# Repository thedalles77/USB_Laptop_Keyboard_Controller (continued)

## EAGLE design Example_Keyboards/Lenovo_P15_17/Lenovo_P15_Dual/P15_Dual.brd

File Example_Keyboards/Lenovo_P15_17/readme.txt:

Use the Lenovo_P15 files for a standard USB keyboard.
The P15_Dual folder is for a separate project that switches a P15 keyboard to its motherboard
or to a different computer that receives the keyboard signals over USB from the Teensy.

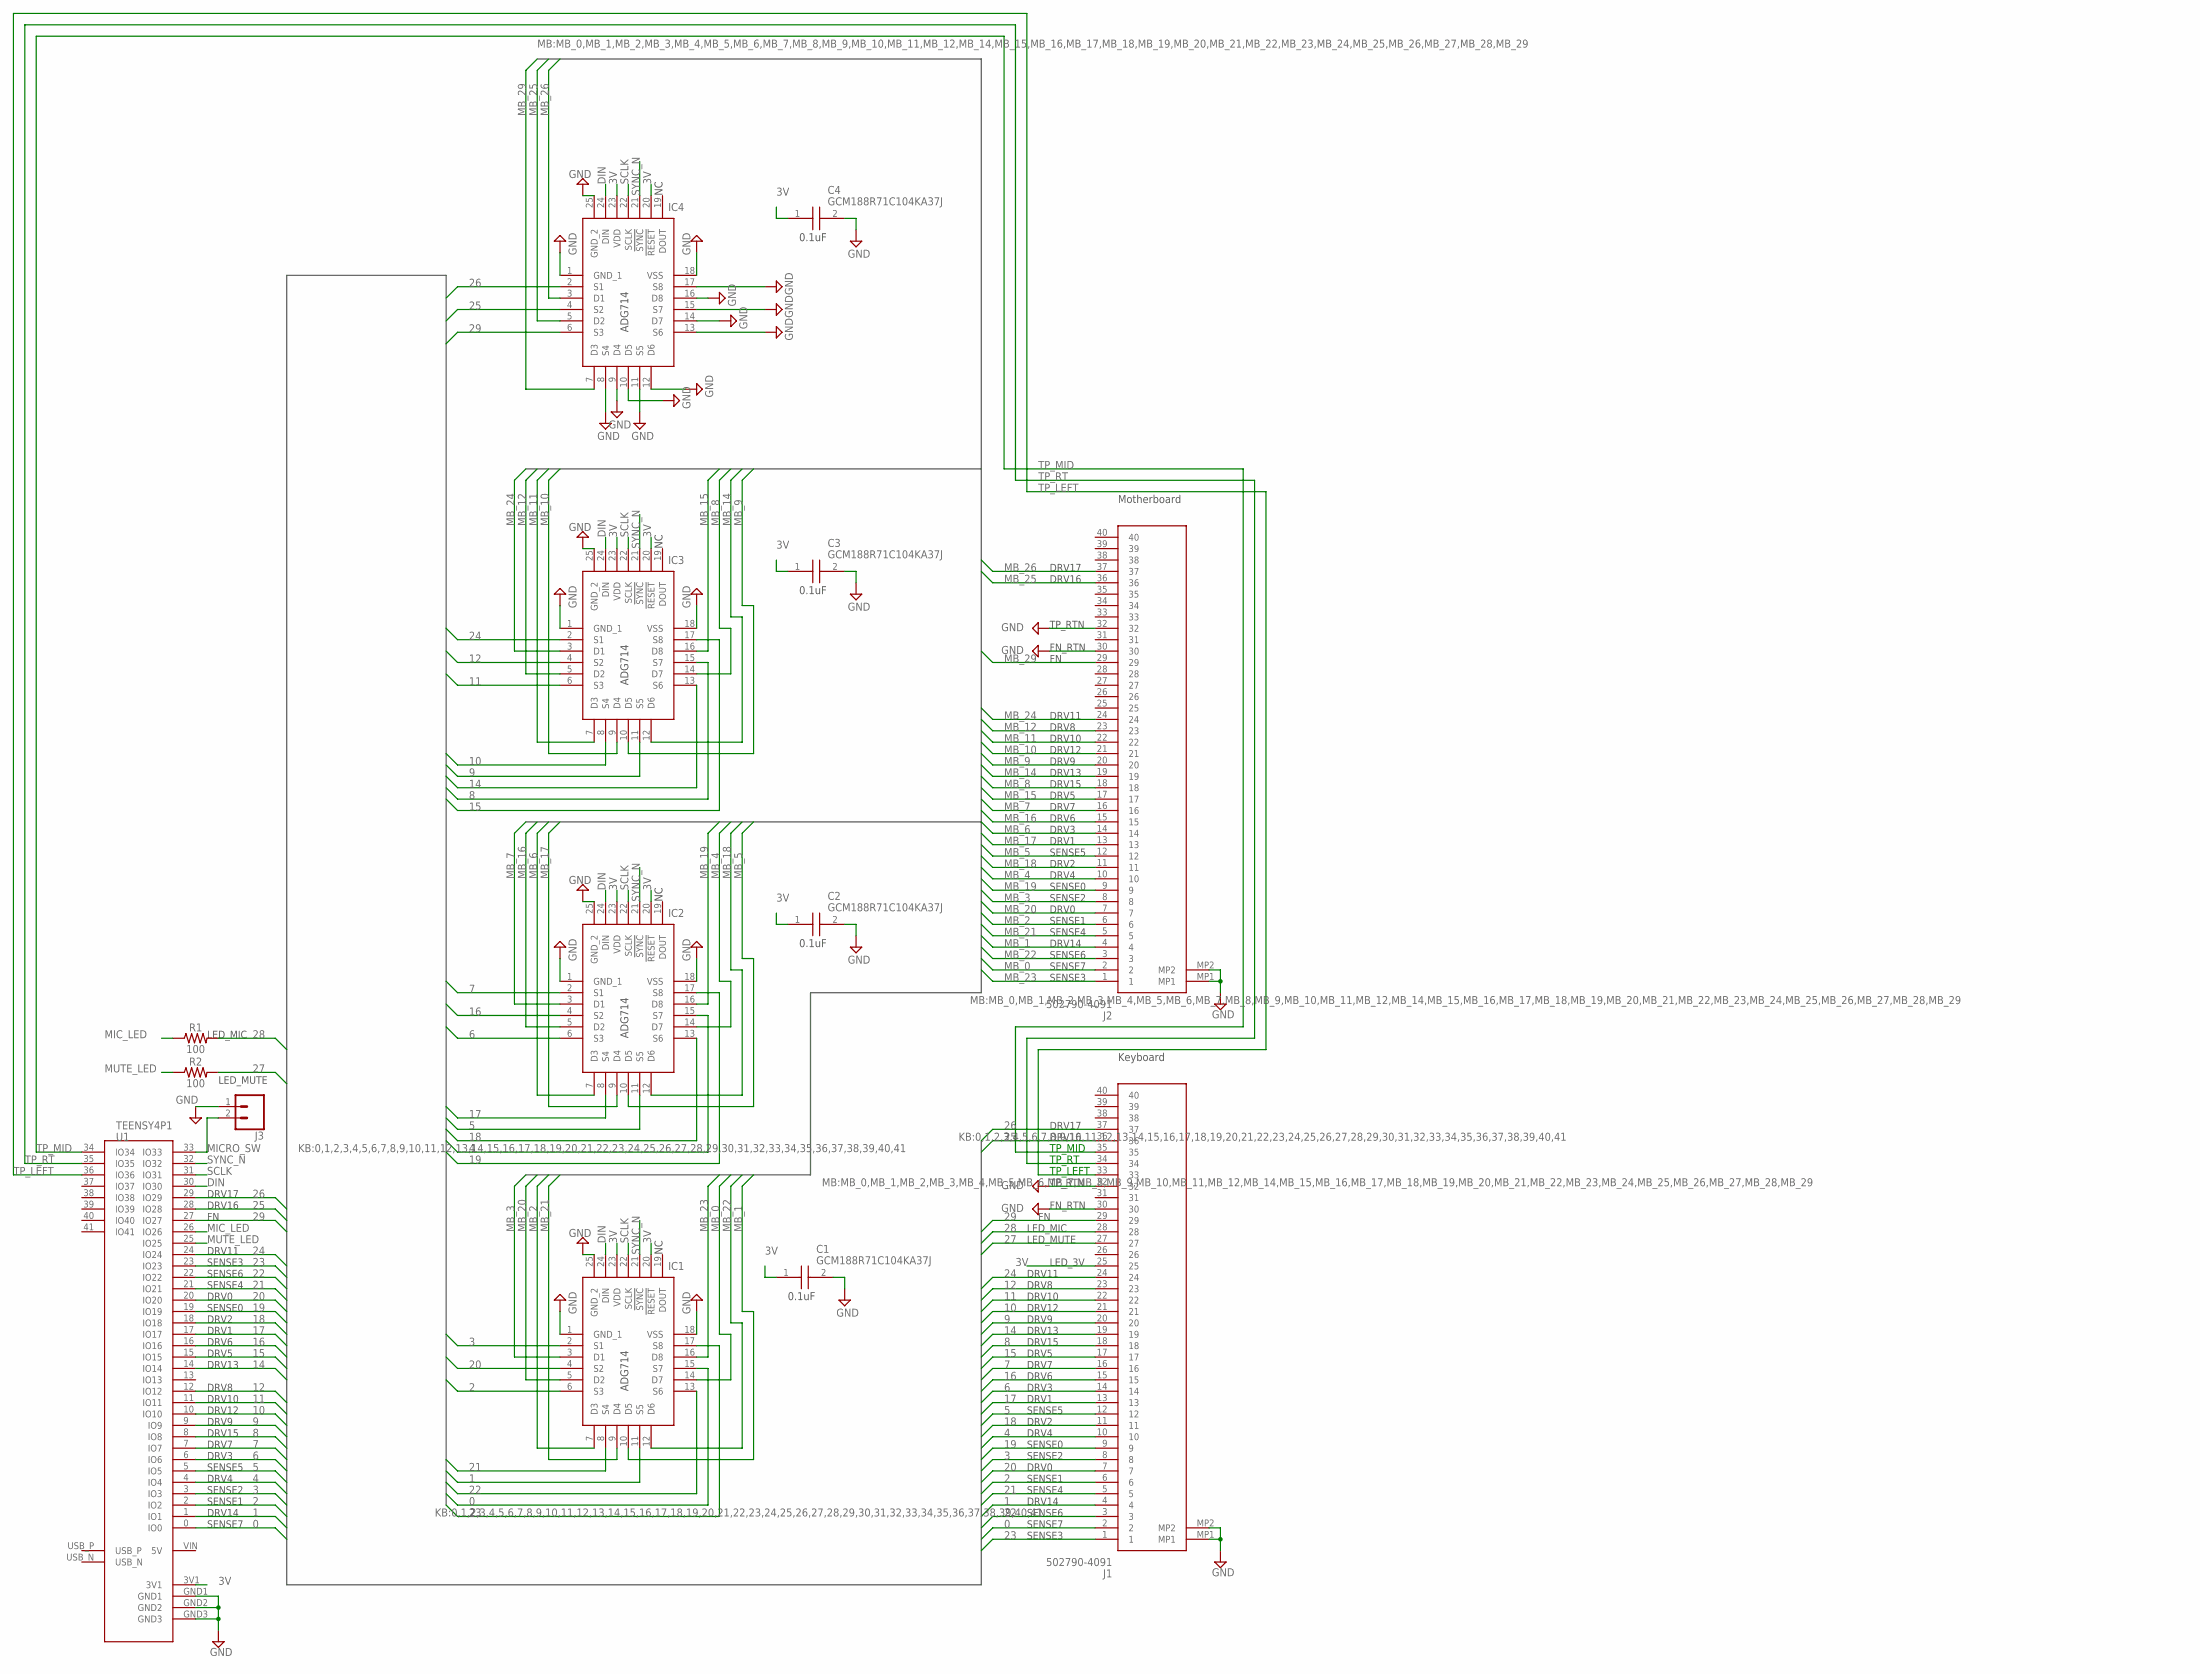
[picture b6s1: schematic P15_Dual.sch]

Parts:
C1, C2, C3, C4: GCM188R71C104KA37J; CAPC1608X90N
IC1, IC2, IC3, IC4: ADG714BCPZ-REEL7; QFN50P400X400X80-25N
J1, J2: 502790-4091; 5027904091
J3: CONN_02; 1X02
R1, R2: 100; 0603_RESISTOR
U1: TEENSY4P1; TEENSY4P1_CUTOUT_USB

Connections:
0: IC1.15 (S7), J1.2, U1.0 (IO0)
1: IC1.11 (S5), J1.4, U1.1 (IO1)
2: IC1.6 (S3), J1.6, U1.2 (IO2)
3: IC1.2 (S1), J1.8, U1.3 (IO3)
3V: C1.1, C2.1, C3.1, C4.1, IC1.20 (!RESET), IC1.23 (VDD), IC2.20 (!RESET), IC2.23 (VDD), IC3.20 (!RESET), IC3.23 (VDD), IC4.20 (!RESET), IC4.23 (VDD), J1.25, U1.3V1
4: IC2.15 (S7), J1.10, U1.4 (IO4)
5: IC2.11 (S5), J1.12, U1.5 (IO5)
6: IC2.6 (S3), J1.14, U1.6 (IO6)
7: IC2.2 (S1), J1.16, U1.7 (IO7)
8: IC3.15 (S7), J1.18, U1.8 (IO8)
9: IC3.11 (S5), J1.20, U1.9 (IO9)
10: IC3.8 (S4), J1.21, U1.10 (IO10)
11: IC3.6 (S3), J1.22, U1.11 (IO11)
12: IC3.4 (S2), J1.23, U1.12 (IO12)
14: IC3.13 (S6), J1.19, U1.14 (IO14)
15: IC3.17 (S8), J1.17, U1.15 (IO15)
16: IC2.4 (S2), J1.15, U1.16 (IO16)
17: IC2.8 (S4), J1.13, U1.17 (IO17)
18: IC2.13 (S6), J1.11, U1.18 (IO18)
19: IC2.17 (S8), J1.9, U1.19 (IO19)
20: IC1.4 (S2), J1.7, U1.20 (IO20)
21: IC1.8 (S4), J1.5, U1.21 (IO21)
22: IC1.13 (S6), J1.3, U1.22 (IO22)
23: IC1.17 (S8), J1.1, U1.23 (IO23)
24: IC3.2 (S1), J1.24, U1.24 (IO24)
25: IC4.4 (S2), J1.36, U1.28 (IO28)
26: IC4.2 (S1), J1.37, U1.29 (IO29)
27: J1.27, R2.2
28: J1.28, R1.2
29: IC4.6 (S3), J1.29, U1.27 (IO27)
DIN: IC1.24 (DIN), IC2.24 (DIN), IC3.24 (DIN), IC4.24 (DIN), U1.30 (IO30)
GND: C1.2, C2.2, C3.2, C4.2, IC1.1 (GND_1), IC1.18 (VSS), IC1.25 (GND_2), IC2.1 (GND_1), IC2.18 (VSS), IC2.25 (GND_2), IC3.1 (GND_1), IC3.18 (VSS), IC3.25 (GND_2), IC4.1 (GND_1), IC4.8 (S4), IC4.9 (D4), IC4.10 (D5), IC4.11 (S5), IC4.12 (D6), IC4.13 (S6), IC4.14 (D7), IC4.15 (S7), IC4.16 (D8), IC4.17 (S8), IC4.18 (VSS), IC4.25 (GND_2), J1.30, J1.32, J1.MP1, J1.MP2, J2.30, J2.32, J2.MP1, J2.MP2, J3.1, U1.GND1, U1.GND2, U1.GND3
MB_0: IC1.14 (D7), J2.2
MB_1: IC1.10 (D5), J2.4
MB_2: IC1.7 (D3), J2.6
MB_3: IC1.3 (D1), J2.8
MB_4: IC2.14 (D7), J2.10
MB_5: IC2.10 (D5), J2.12
MB_6: IC2.7 (D3), J2.14
MB_7: IC2.3 (D1), J2.16
MB_8: IC3.14 (D7), J2.18
MB_9: IC3.10 (D5), J2.20
MB_10: IC3.9 (D4), J2.21
MB_11: IC3.7 (D3), J2.22
MB_12: IC3.5 (D2), J2.23
MB_14: IC3.12 (D6), J2.19
MB_15: IC3.16 (D8), J2.17
MB_16: IC2.5 (D2), J2.15
MB_17: IC2.9 (D4), J2.13
MB_18: IC2.12 (D6), J2.11
MB_19: IC2.16 (D8), J2.9
MB_20: IC1.5 (D2), J2.7
MB_21: IC1.9 (D4), J2.5
MB_22: IC1.12 (D6), J2.3
MB_23: IC1.16 (D8), J2.1
MB_24: IC3.3 (D1), J2.24
MB_25: IC4.5 (D2), J2.36
MB_26: IC4.3 (D1), J2.37
MB_29: IC4.7 (D3), J2.29
MICRO_SW: J3.2, U1.33 (IO33)
MIC_LED: R1.1, U1.26 (IO26)
MUTE_LED: R2.1, U1.25 (IO25)
SCLK: IC1.22 (SCLK), IC2.22 (SCLK), IC3.22 (SCLK), IC4.22 (SCLK), U1.31 (IO31)
SYNC_N: IC1.21 (!SYNC), IC2.21 (!SYNC), IC3.21 (!SYNC), IC4.21 (!SYNC), U1.32 (IO32)
TP_LEFT: J1.33, U1.36 (IO36)
TP_MID: J1.35, U1.34 (IO34)
TP_RT: J1.34, U1.35 (IO35)

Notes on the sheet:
Keyboard
Motherboard
ADG714
0.1uF
DRV17
DRV16
LED_MIC
LED_MUTE
TP_RTN
FN_RTN
DRV11
LED_3V
DRV8
DRV10
DRV12
DRV9
DRV13
DRV15
DRV5
DRV7
DRV6
DRV3
DRV1
SENSE5
DRV2
DRV4
SENSE0
SENSE2
DRV0
SENSE4
SENSE1
DRV14
SENSE6
SENSE7
SENSE3
TP_RT
TP_LEFT
TP_MID

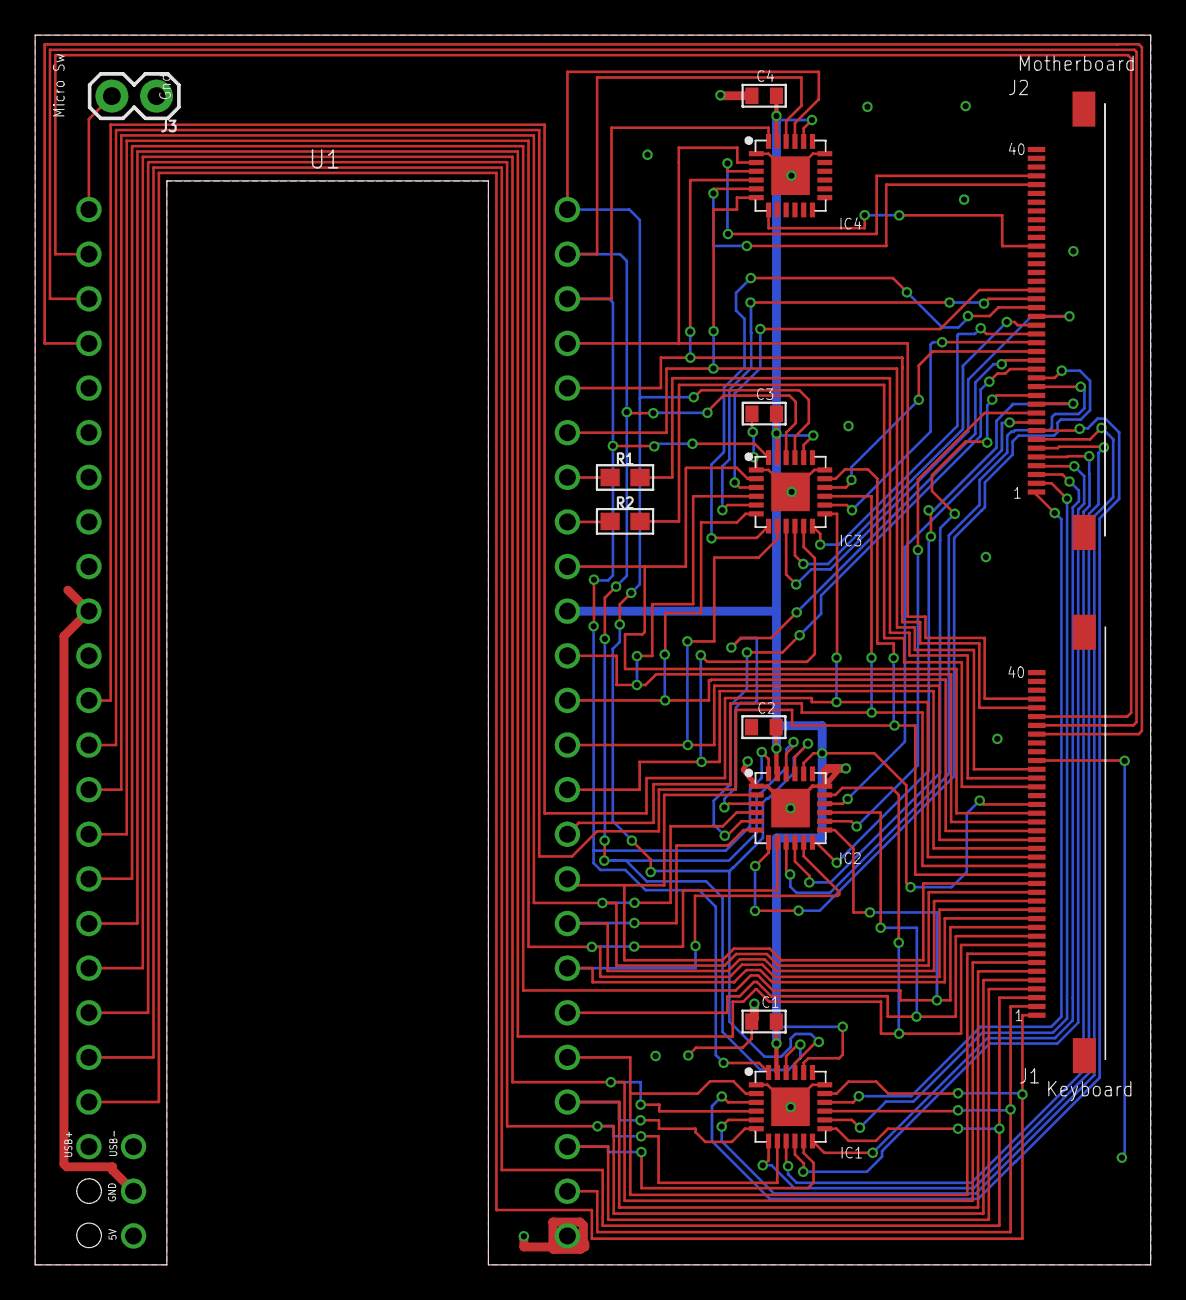
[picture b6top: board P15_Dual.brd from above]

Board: 2 copper layers, 63.5 x 70.0 mm, 14 parts (0 on the bottom side), 67 nets.

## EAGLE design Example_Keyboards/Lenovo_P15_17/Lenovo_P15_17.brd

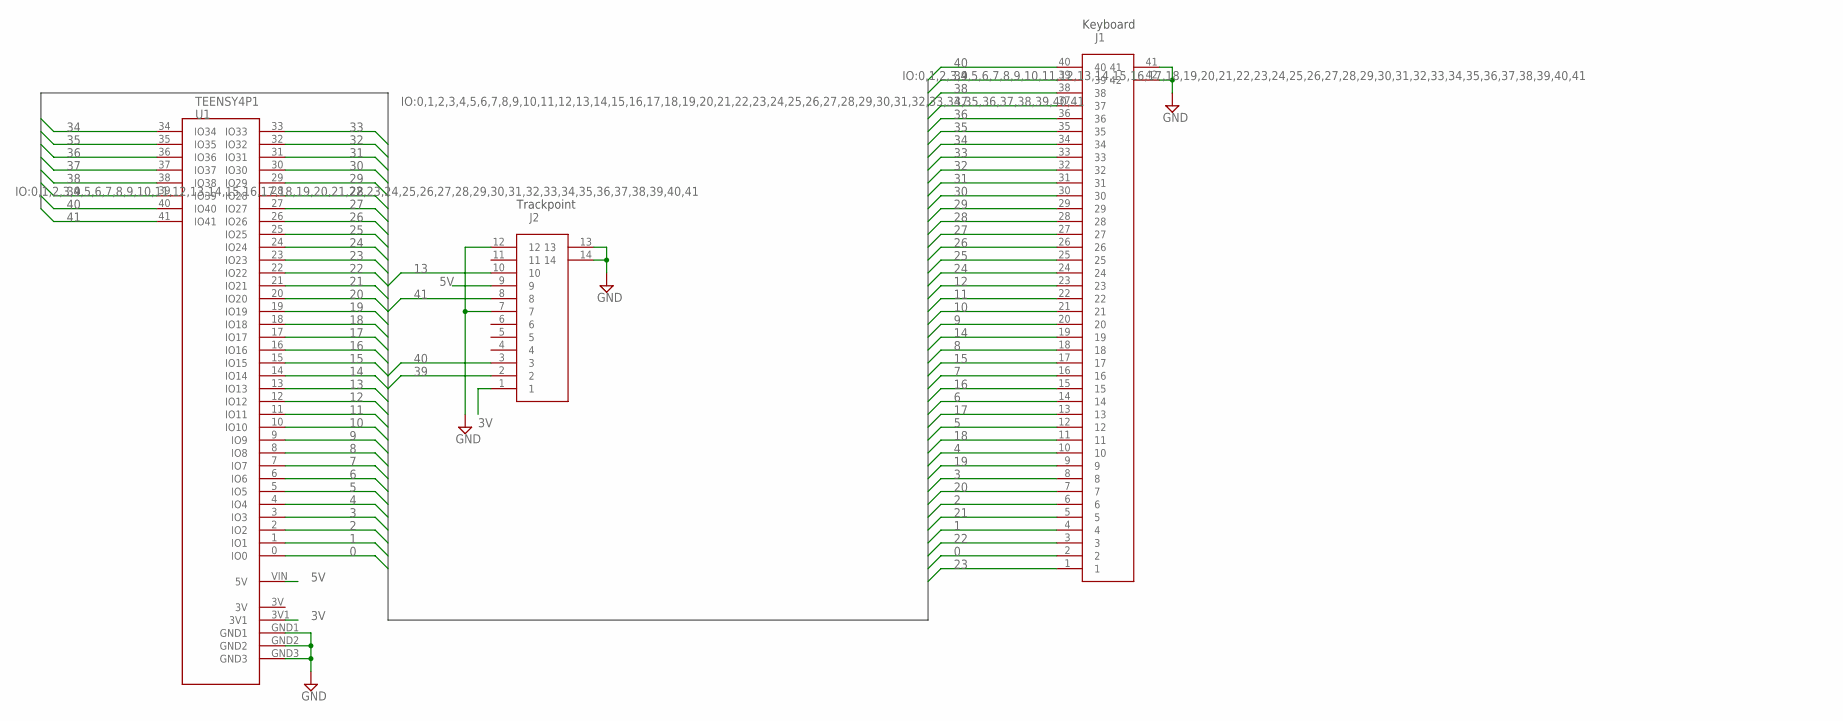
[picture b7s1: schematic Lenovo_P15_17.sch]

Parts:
J1: FPC34_P5MM
J2: FPC12
U1: TEENSY4P1; TEENSY4P0_CUTOUT

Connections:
0: J1.2, U1.0 (IO0)
1: J1.4, U1.1 (IO1)
2: J1.6, U1.2 (IO2)
3: J1.8, U1.3 (IO3)
3V: J2.1, U1.3V1
4: J1.10, U1.4 (IO4)
5: J1.12, U1.5 (IO5)
5V: J2.9, U1.VIN (5V)
6: J1.14, U1.6 (IO6)
7: J1.16, U1.7 (IO7)
8: J1.18, U1.8 (IO8)
9: J1.20, U1.9 (IO9)
10: J1.21, U1.10 (IO10)
11: J1.22, U1.11 (IO11)
12: J1.23, U1.12 (IO12)
13: J2.10, U1.13 (IO13)
14: J1.19, U1.14 (IO14)
15: J1.17, U1.15 (IO15)
16: J1.15, U1.16 (IO16)
17: J1.13, U1.17 (IO17)
18: J1.11, U1.18 (IO18)
19: J1.9, U1.19 (IO19)
20: J1.7, U1.20 (IO20)
21: J1.5, U1.21 (IO21)
22: J1.3, U1.22 (IO22)
23: J1.1, U1.23 (IO23)
24: J1.24, U1.24 (IO24)
25: J1.25, U1.25 (IO25)
26: J1.26, U1.26 (IO26)
27: J1.27, U1.27 (IO27)
28: J1.28, U1.28 (IO28)
29: J1.29, U1.29 (IO29)
30: J1.30, U1.30 (IO30)
31: J1.31, U1.31 (IO31)
32: J1.32, U1.32 (IO32)
33: J1.33, U1.33 (IO33)
34: J1.34, U1.34 (IO34)
35: J1.35, U1.35 (IO35)
36: J1.36, U1.36 (IO36)
37: J1.37, U1.37 (IO37)
38: J1.38, U1.38 (IO38)
39: J1.39, J2.2, U1.39 (IO39)
40: J1.40, J2.3, U1.40 (IO40)
41: J2.8, U1.41 (IO41)
GND: J1.41, J1.42, J2.7, J2.12, J2.13, J2.14, U1.GND1, U1.GND2, U1.GND3

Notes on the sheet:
Trackpoint
Keyboard

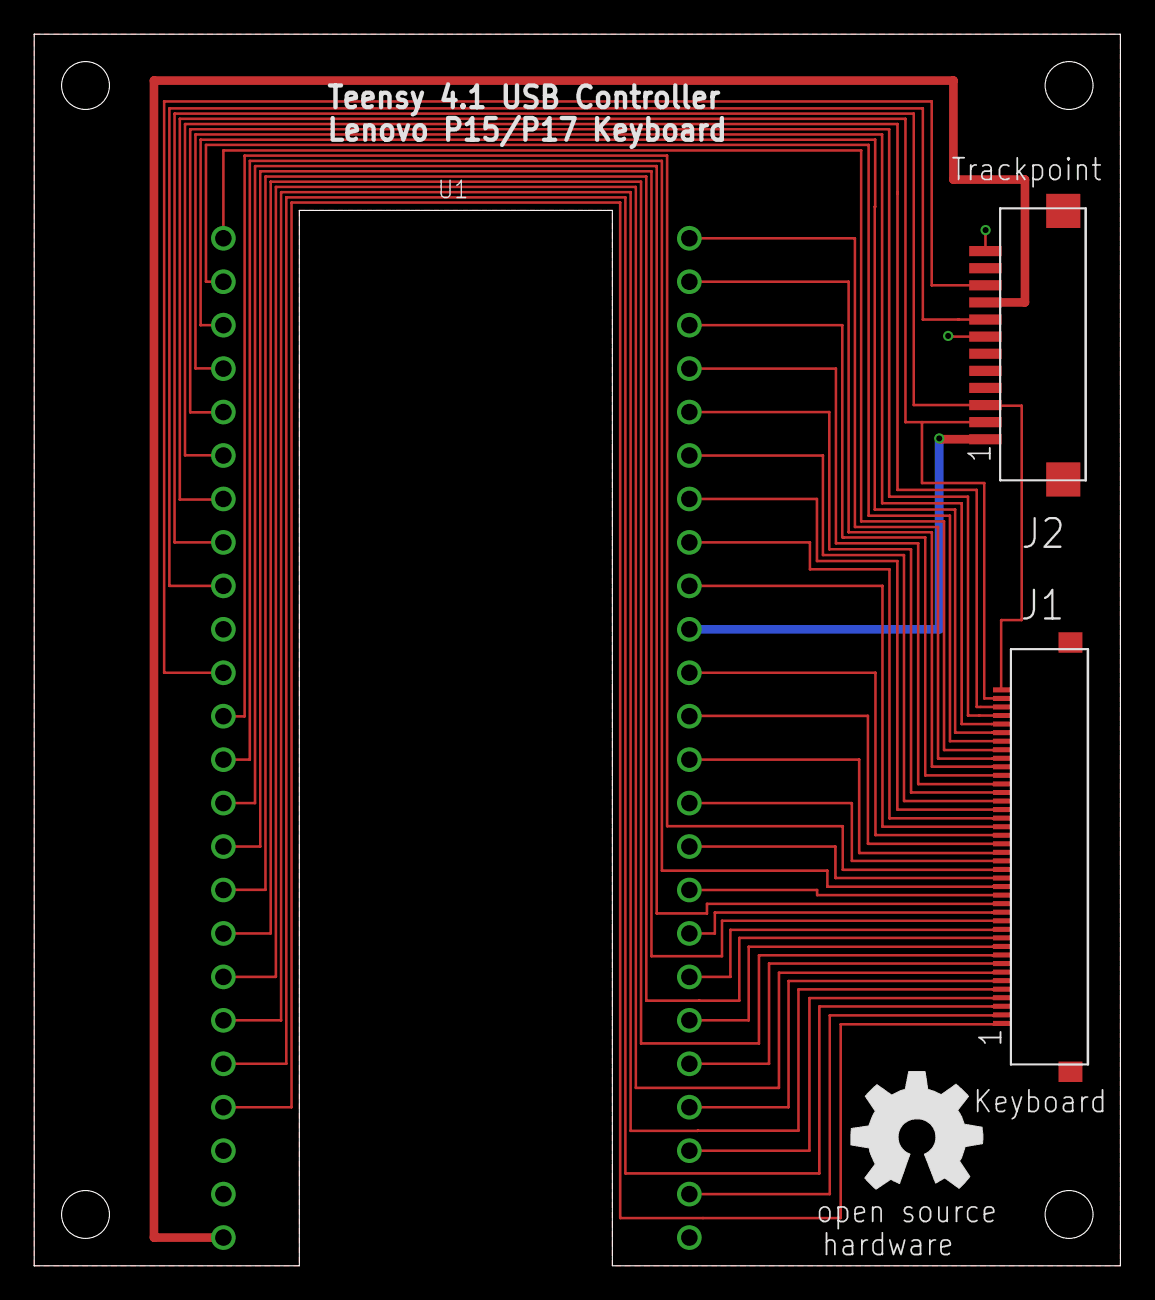
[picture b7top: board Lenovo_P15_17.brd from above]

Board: 2 copper layers, 63.5 x 72.0 mm, 5 parts (0 on the bottom side), 45 nets.

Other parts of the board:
U$1, U$2: OSHW_8MM

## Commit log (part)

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2024-06-19 Add files via upload
    Added TP current and Adafruit links
2024-10-07 Update README.md
    Added No_solder_method.pdf file
2025-01-17 Update Matrix_Decoder_2pp_RevA.ino
    Changed min_pin to 1 instead of 3
2025-11-07 Correct KiCad spelling
